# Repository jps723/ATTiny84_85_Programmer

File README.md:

# ATTiny Programming Jig Build Notes                                                                    	1/5/20
 
This project is in partnership with [Bantam Tools](https://www.bantamtools.com)

**Design Notes:**

**LEDs**
Arduino pins 7, 8, and 9 are attached to LEDs to show Programming/Errors/Heartbeat, respectively.  These are status LEDs during programming and built into the ArduinoISP sketch.  The yellow LED ‘breathes’ when the programmer is connected, the green led blinks when programming is underway, and the red LED turns on when there is an error and when the sketch finishes uploading. 
 
```
7 — Programming
8 — Errors
9 — Heartbeat
```
 
**SPI PROGRAMMING**
```
10 — SS (Slave Select)
11 — (MOSI)
12 — (MISO)
13 — (SCK)
```
 
**GLOBAL**
```
5v — Power
GND — GND
Reset
```
 
**Build Process**
It’s easiest to solder in this order:
```
1. Resistors
2. Dip Sockets
3. Headers
4. LEDs
5. Capacitor
```
 
**Programming Process**
```
1. Upload ArduinoISP Sketch to the Arduino Uno
2. Install ATTinyCore by Spence Konde via the Arduino Board Manager
3. Tools > Board > ATTiny 25/45/85 (or 24/44/84)
4. Tools > Clock - 8 MHz (Internal) 
5. Tools > Chip > ATTiny85 (or ATTiny84)
6. Tools > LTO – “Disabled”
7. The remaining settings should remain as default.
8. Plug the ATTiny into the socket; With the Arduino’s USB port pointing down, pin 1 should be on the lower right
9. Plug the jig into the Arduino and power it (the yellow LED should begin to ‘breathe’ after a startup sequence)
10.  Tools > Burn Bootloader (This only needs to be done once per chip)
```
 
**Test**
```
1. File > Examples > 01.Basics > Blink; change LED pin to 3 (this is pin2 on the 85, pin10 on the 84)
2. Tools > Programmer: Arduino as ISP
3. Sketch > Upload using Programmer
```

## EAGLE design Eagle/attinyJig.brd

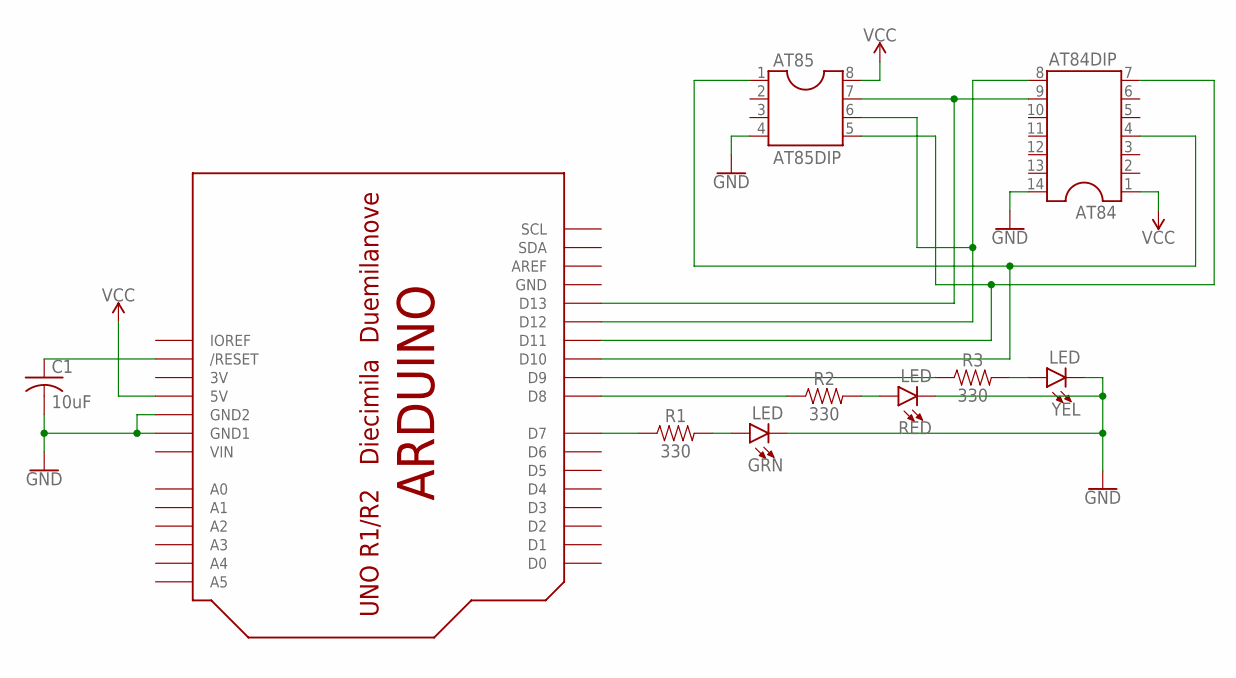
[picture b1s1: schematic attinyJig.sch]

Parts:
AT84: AT84DIP; DIL14
AT85: AT85DIP; DIL08
C1: 10uF; C025-024X044
GRN: LED; LED_3MM-NS
R1, R2, R3: 330; AXIAL-0.3
RED: LED; LED_3MM-NS
UNO1: UNO; ARDUINOUNO_NOPROTO
YEL: LED; LED_3MM-NS

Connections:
3V: UNO1.3V
GND: AT84.14, AT85.4, C1.2, GRN.K (C), RED.K (C), UNO1.GND, UNO1.GND1, UNO1.GND2, YEL.K (C)
unnamed: R2.P$1 (1), UNO1.D8
unnamed: R3.P$1 (1), UNO1.D9
unnamed: GRN.A, R1.P$2 (2)
unnamed: R2.P$2 (2), RED.A
unnamed: R3.P$2 (2), YEL.A
unnamed: C1.1, UNO1.RESET (/RESET)
unnamed: AT84.4, AT85.1, UNO1.D10
unnamed: AT84.9, AT85.7, UNO1.D13
unnamed: AT84.8, AT85.6, UNO1.D12
unnamed: R1.P$1 (1), UNO1.D7
unnamed: AT84.7, AT85.5, UNO1.D11
VCC: AT84.1, AT85.8, UNO1.5V
VIN: UNO1.VIN

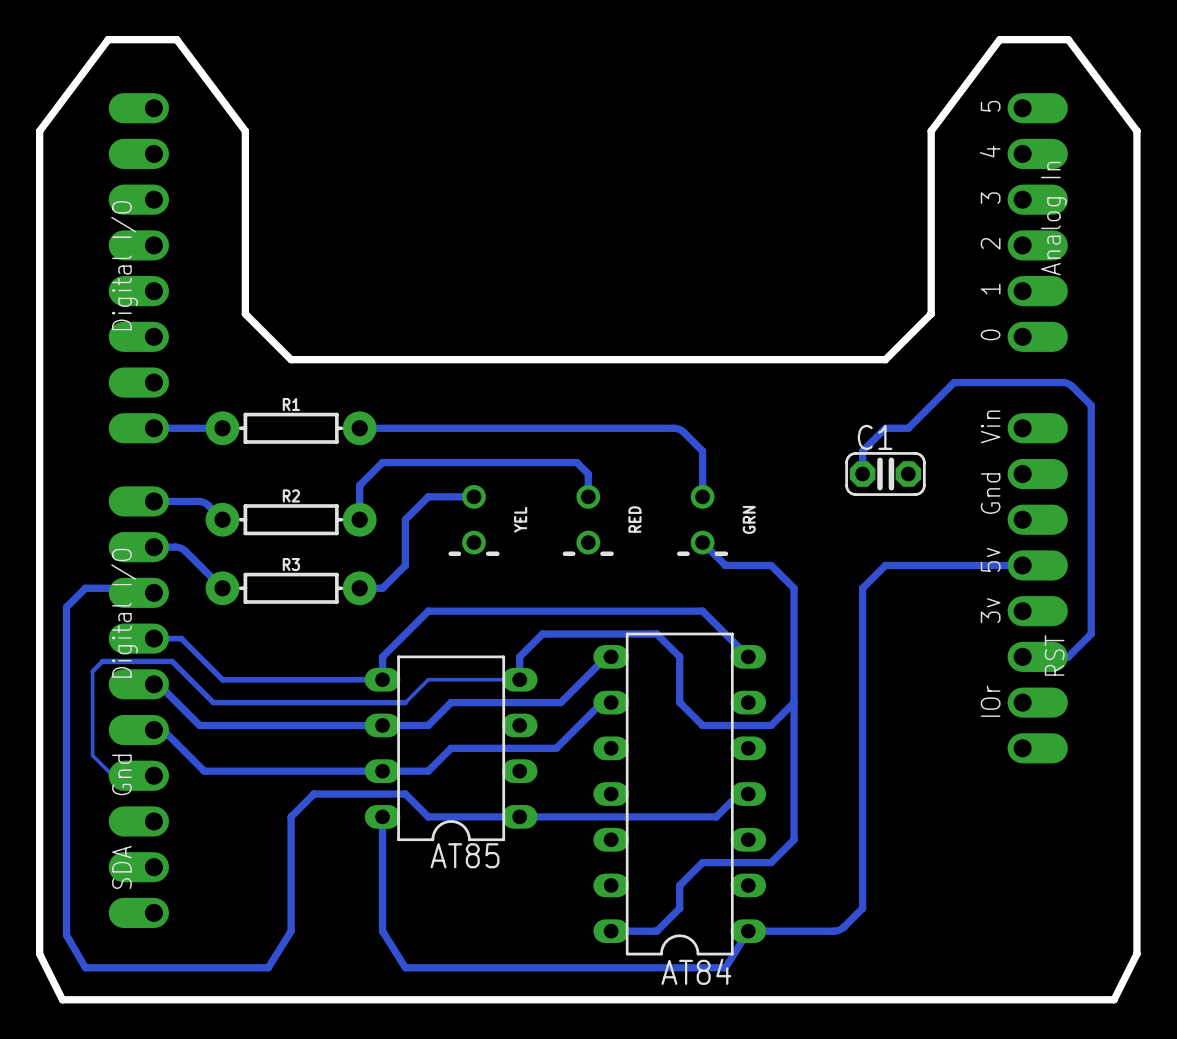
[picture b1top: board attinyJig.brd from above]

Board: 2 copper layers, 61.0 x 53.3 mm, 10 parts (0 on the bottom side), 13 nets.

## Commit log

2020-10-30 added bantam tools credit

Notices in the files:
parts and their libraries:
SparkFun-Resistors: Licensing: Creative Commons ShareAlike 4.0 International - https://creativecommons.org/licenses/by-sa/4.0
